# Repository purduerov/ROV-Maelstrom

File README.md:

# ROV-Maelstrom

Purdue IEEE designed an ROV (Remotely Operated underwater Vehicle) to compete in the 2016 [MATE international competition](http://www.marinetech.org/rov-competition-2/). ROV *Maelstrom* was the cumulation of this effort that resulted in a 13th place finish. For more information visit [purdueieee.org/rov](http://purdueieee.org/rov).

Our design is hearby open-sourced in order to share what we have done with other MATE teams and those who are interested. While not all of our designs worked as planned, we share these files in order to assist thoughs who may need it and inspire others with these ideas.

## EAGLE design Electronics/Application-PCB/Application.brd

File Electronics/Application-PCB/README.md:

# PCB-Maelstrom-Application
The application board was intended to contains mission specific electronics including the special manipulators, temperature sensors, pressure sensors, LED drivers, and solenoids for the claw. These components would be grouped together on this board to simplify the more complex microcontroller board with their own chip, the STM 32F405-64 PIN, to provide the interface. 

This board was planned before the mission description, but then we realized that the mission required significantly fewer tools than expected and it was easier to relocate the tooling circuitry to the main microcontroller board. However, a board was still designed for some extra features but it was never tested or implemented due to time constraints. The application board ended up including the LED drivers and the backup temperature sensor’s circuit. We kept the STM32F405-64 pin microcontroller from the original design. It also included a micro-USB for programming the STM chip, a CAN communication chip and some debugging LEDs. The LED driver was modeled to use the LM3409HV FET buck controller.

# LED driver overview
- Controlled by Texas Instruments LM3409HV Buck Controller
- Steps down Application board 12V power to 6V, 0.5A max
- Output current adjustable via PWM to allow for LED dimming
- Drives two high power white LEDs

# Main considerations taken in design of the board:
	- No ground plane or traces opposite the inductor avoid effects of eddy currents
	- Input capacitors located as close to the chip power pins on the same layer
	- Drain of PFET connected as close as possible to power inductor, with minimal trace area
	- Place output capacitor close to the inductor
	- At least 4 thermal vias located under the buck controller thermal pad for heat dissipation	
	- Isolate small signal ground (IC ground) from the power ground
	- Minimise the use of vias for the power ground
	- Isolate noise-causing components (diode, inductor, PWM signal) away from other components
	- In particular, below are the recommendations for designing the feedback route. However the design of our particular driver makes them somewhat irrelevant:
		a). Feedback terminal of IC which inputs feedback signal, is normally designed with high impedance. Output of this terminal and
		resistor crossover network must be connected with short wire.
		b). Part which detects the output voltage must be connected after output capacitor or at both ends of output capacitor.
		c). Wiring the resistor-divider circuit nearby and parallel, makes it better for noise tolerance.
		d). Draw wire far away from switching node of inductor and diode. Do not wire directly below the inductor and diode, and not
		parallel to power supply line. Multilayer board must be also wired in the same way. 
	- Proper land pattern of power components to minimize impedance: (Application Notes 136, Page 7)
		http://cds.linear.com/docs/en/application-note/an136f.pdf

(recommendations drawn from: http://rohmfs.rohm.com/en/products/databook/applinote/ic/power/switching_regulator/converter_pcb_layout_appli-e.pdf)

# Possible changes/improvements:
	- decrease the board area
	
# Thoughts:
	- The board schematic was based off the 'Typical Applications' under section 8.2 of the Buck Controller datasheet. For some reason that design does not have a output capacitor, unlike standard buck controller designs
	- The design mentioned above also uses a different feedback system compared to the standard; namely it only uses 1 resistor instead of 2

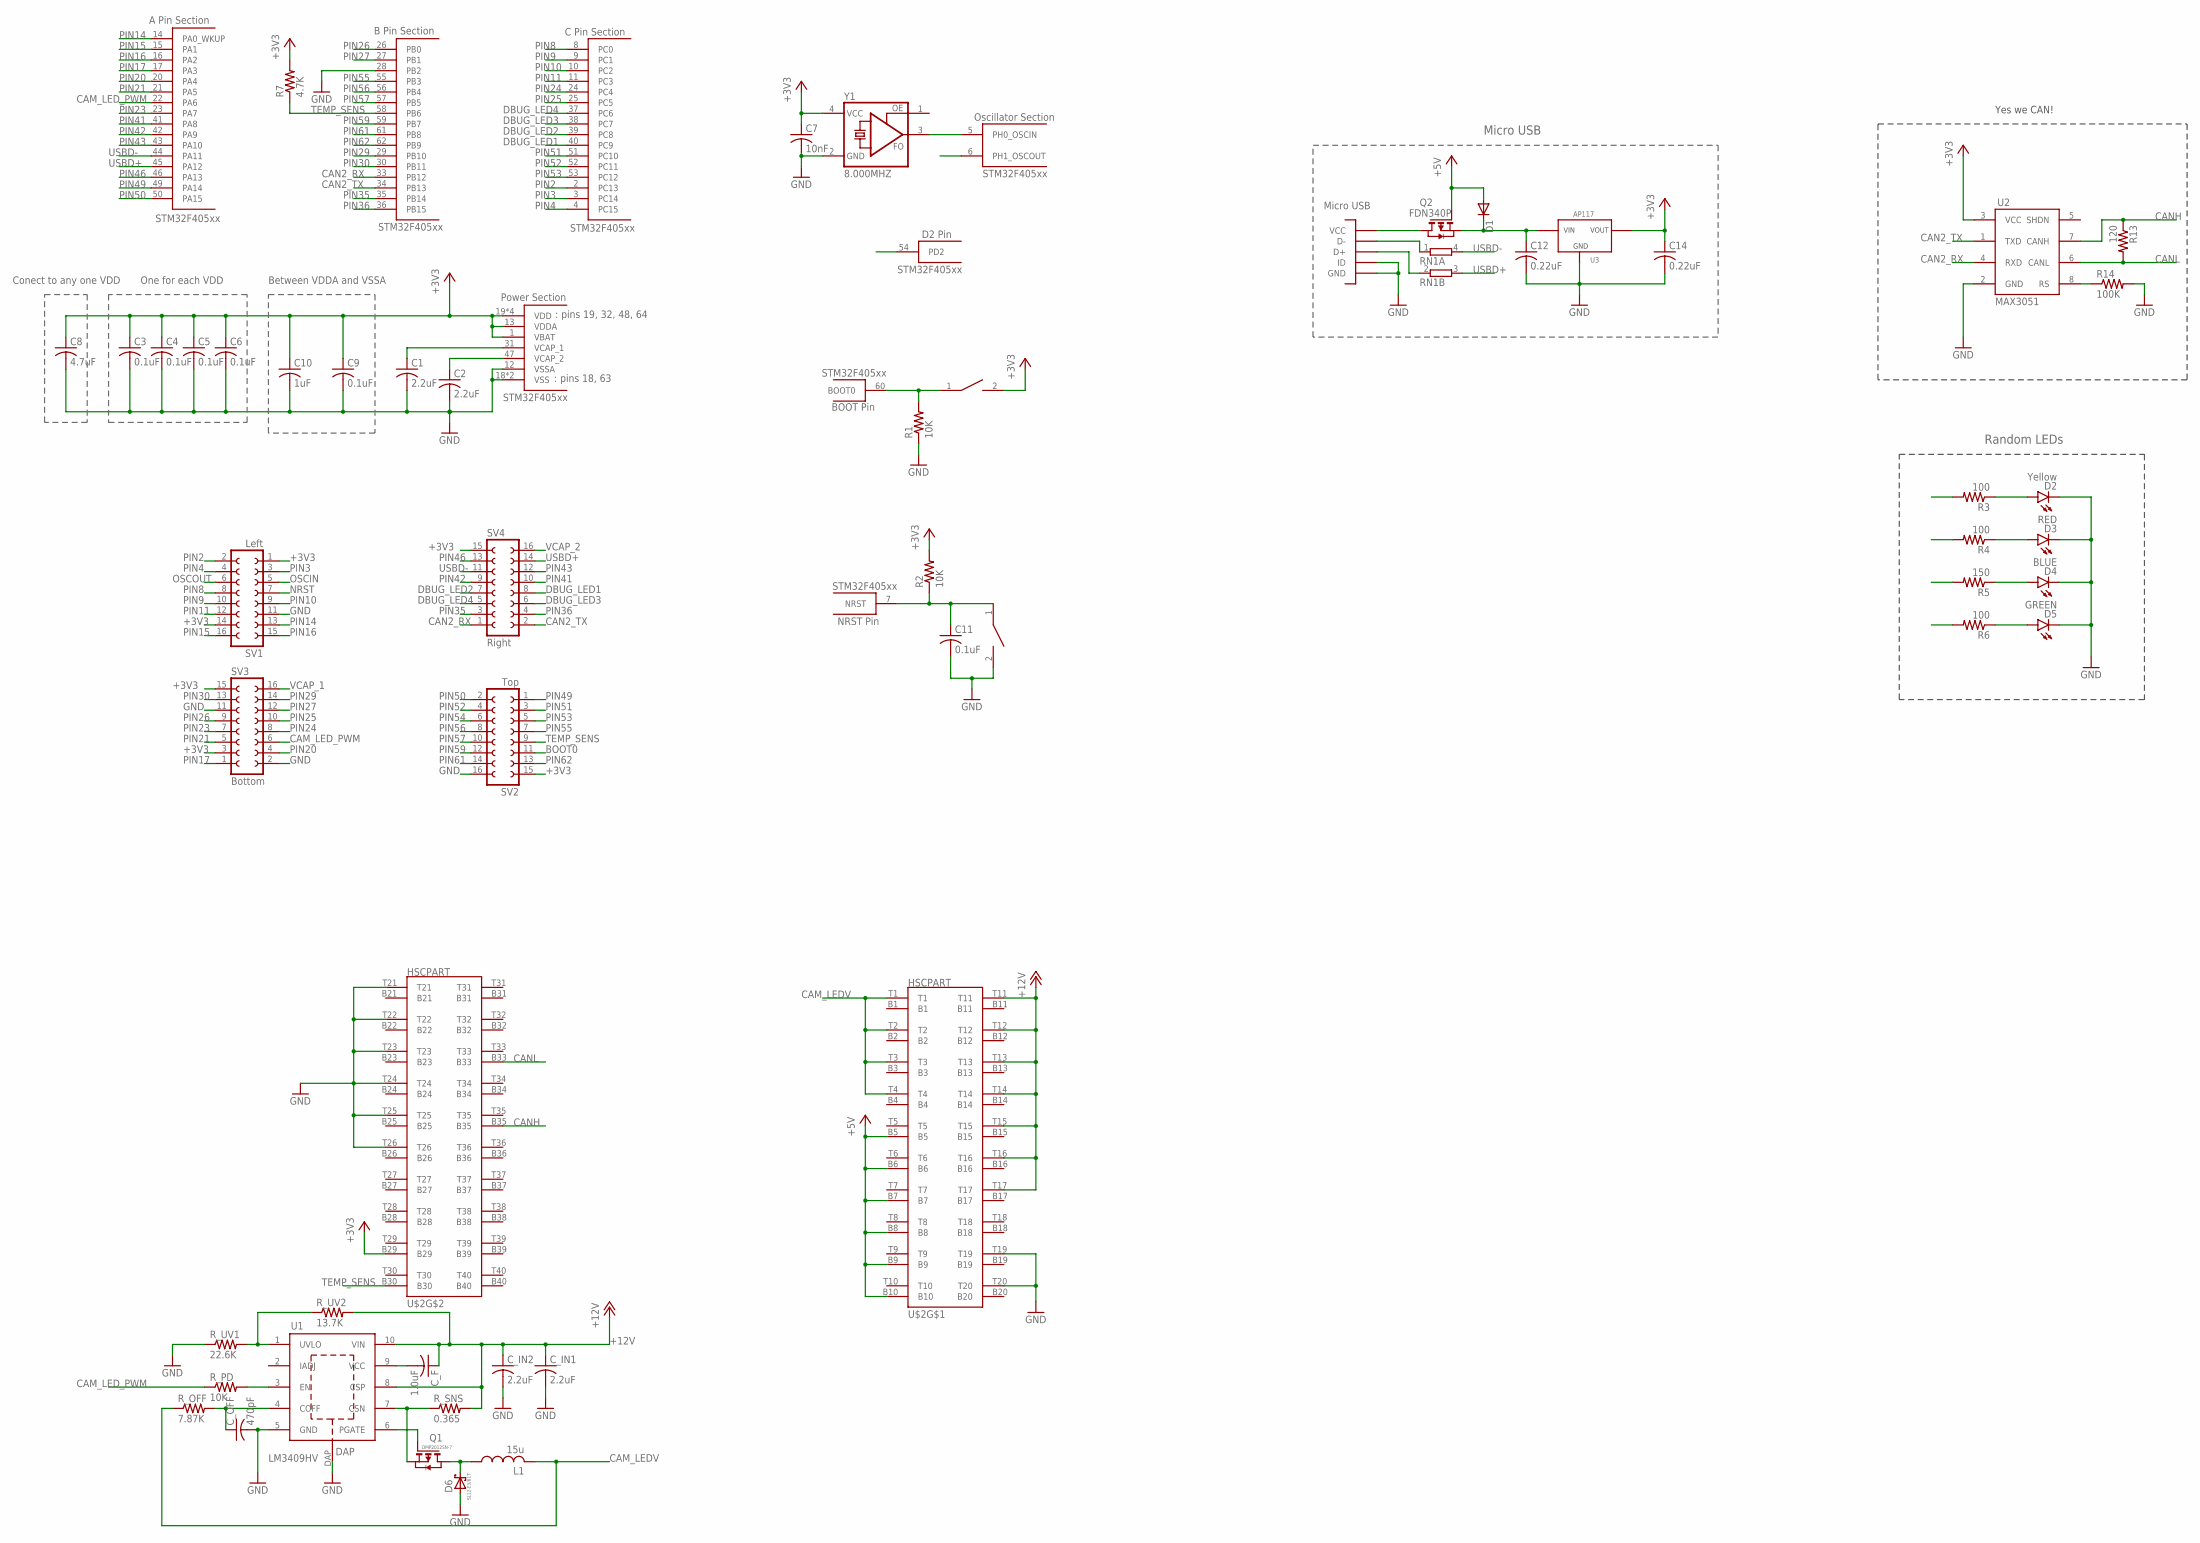
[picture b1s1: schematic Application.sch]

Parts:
C1, C2: 2.2uF; C0603
C3, C4, C5, C6, C9, C11: 0.1uF; C0603
C7: 10nF; C0603
C8: 4.7uF; C0603
C10: 1uF; C0603
C12, C14: 0.22uF; C0603
C_F: 1.0uF; C0603
C_IN1, C_IN2: 2.2uF; C0603
C_OFF: 470pF; C0603
D1: DIODE-DO-214AC; DO-214AC
D2: Yellow; LED-0603
D3: RED; LED-0603
D4: BLUE; LED-0603
D5: GREEN; LED-0603
D6: SL12-E3/61T
L1: 15u; SRN8040
Q1: DMP2012SN-7
Q2: FDN340P; SOT-23
R1, R2: 10K; R0603
R3, R4, R6: 100; R0603
R5: 150; R0603
R7: 4.7K; R0603
R13: 120; R0603
R14: 100K; R0603
RN1: 2R-NEXBV4V; EXBV4V
R_OFF: 7.87K; R0603
R_PD: 10K; R0603
R_SNS: 0.365; R2512
R_UV1: 22.6K; R0603
R_UV2: 13.7K; R0603
S1: BOOT; SW_2512
S2: RESET; SW_2512
SV1: Left; FE08-2
SV2: Top; FE08-2
SV3: Bottom; FE08-2
SV4: Right; FE08-2
U1: LM3409HV; VSSOP-10
U2: MAX3051; SOT23-8L
U3: U3; SOT223
U4: STM32F405; LQFP64
U5: MICROUSB; MICRO_B
U$2: HSCPART; HSC8-40PINOUUT
Y1: 8.000MHZ; ASF

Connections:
+3V3: C3.1, C4.1, C5.1, C6.1, C7.1, C8.1, C9.1, C10.1, C14.1, R2.2, R7.2, S1.2, SV1.1, SV1.14, SV2.15, SV3.3, SV3.15, SV4.15, U2.3 (VCC), U3.TAB (VOUT), U3.VOUT, U4.1 (VBAT), U4.13 (VDDA), U4.19 (VDD), U4.32 (VDD), U4.48 (VDD), U4.64 (VDD), U$2.B29, Y1.4 (VCC)
+5V: D1.A, Q2.3 (G), U$2.B5, U$2.B6, U$2.B7, U$2.B8, U$2.B9, U$2.B10
+12V: C_F.1, C_IN1.1, C_IN2.1, R_SNS.2, R_UV2.2, U1.8 (CSP), U1.10 (VIN), U$2.T11, U$2.T12, U$2.T13, U$2.T14, U$2.T15, U$2.T16, U$2.T17
BOOT0: R1.2, S1.1, SV2.11, U4.60 (BOOT0)
CAM_LEDV: L1.2, R_OFF.1, U$2.T1, U$2.T2, U$2.T3, U$2.T4
CAM_LED_PWM: R_PD.1, SV3.6, U4.22 (PA6)
CAN2_RX: SV4.1, U2.4 (RXD), U4.33 (PB12)
CAN2_TX: SV4.2, U2.1 (TXD), U4.34 (PB13)
CANH: R13.1, U2.7 (CANH), U$2.B35
CANL: R13.2, U2.6 (CANL), U$2.B33
DBUG_LED1: R3.2, SV4.8, U4.40 (PC9)
DBUG_LED2: R4.2, SV4.7, U4.39 (PC8)
DBUG_LED3: R5.2, SV4.6, U4.38 (PC7)
DBUG_LED4: R6.2, SV4.5, U4.37 (PC6)
GND: C1.2, C2.2, C3.2, C4.2, C5.2, C6.2, C7.2, C8.2, C9.2, C10.2, C11.2, C12.2, C14.2, C_IN1.2, C_IN2.2, C_OFF.2, D2.C, D3.C, D4.C, D5.C, D6.2 (A), R1.1, R14.2, R_UV1.1, S2.2, SV1.11, SV2.16, SV3.2, SV3.11, U1.5 (GND), U1.DAP, U2.2 (GND), U3.GND, U4.12 (VSSA), U4.18 (VSS), U4.28 (PB2), U4.63 (VSS), U5.GND1 (GND), U5.GND2 (GND), U5.GND3 (GND), U5.GND4 (GND), U5.GND7 (GND), U5.GND8 (GND), U5.P4 (ID), U5.P5 (GND), U$2.T19, U$2.T20, U$2.T21, U$2.T22, U$2.T23, U$2.T24, U$2.T25, U$2.T26, Y1.2 (GND)
L1: D6.1 (C), L1.1, Q1.1 (D)
unnamed: RN1.1, U5.P2 (D-)
unnamed: R_UV1.2, R_UV2.1, U1.1 (UVLO)
unnamed: C_OFF.1, R_OFF.2, U1.4 (COFF)
unnamed: C_F.2, U1.9 (VCC)
unnamed: Q1.3 (S), R_SNS.1, U1.7 (CSN)
unnamed: R_PD.2, U1.3 (EN)
unnamed: Q1.2 (G), U1.6 (PGATE)
unnamed: RN1.2 (1), U5.P3 (D+)
unnamed: Q2.1 (D), U5.P1 (VCC)
unnamed: C12.1, D1.C, Q2.2 (S), U3.VIN
unnamed: D2.A, R3.1
unnamed: D3.A, R4.1
unnamed: D4.A, R5.1
unnamed: D5.A, R6.1
unnamed: R14.1, U2.8 (RS)
NRST: C11.1, R2.1, S2.1, SV1.7, U4.7 (NRST)
OSCIN: SV1.5, U4.5 (PH0_OSCIN), Y1.3 (FO)
OSCOUT: SV1.6, U4.6 (PH1_OSCOUT)
PIN2: SV1.2, U4.2 (PC13)
PIN3: SV1.3, U4.3 (PC14)
PIN4: SV1.4, U4.4 (PC15)
PIN8: SV1.8, U4.8 (PC0)
PIN9: SV1.10, U4.9 (PC1)
PIN10: SV1.9, U4.10 (PC2)
PIN11: SV1.12, U4.11 (PC3)
PIN14: SV1.13, U4.14 (PA0_WKUP)
PIN15: SV1.16, U4.15 (PA1)
PIN16: SV1.15, U4.16 (PA2)
PIN17: SV3.1, U4.17 (PA3)
PIN20: SV3.4, U4.20 (PA4)
PIN21: SV3.5, U4.21 (PA5)
PIN23: SV3.7, U4.23 (PA7)
PIN24: SV3.8, U4.24 (PC4)
PIN25: SV3.10, U4.25 (PC5)
PIN26: SV3.9, U4.26 (PB0)
PIN27: SV3.12, U4.27 (PB1)
PIN29: SV3.14, U4.29 (PB10)
PIN30: SV3.13, U4.30 (PB11)
PIN35: SV4.3, U4.35 (PB14)
PIN36: SV4.4, U4.36 (PB15)
PIN41: SV4.10, U4.41 (PA8)
PIN42: SV4.9, U4.42 (PA9)
PIN43: SV4.12, U4.43 (PA10)
PIN46: SV4.13, U4.46 (PA13)
PIN49: SV2.1, U4.49 (PA14)
PIN50: SV2.2, U4.50 (PA15)
PIN51: SV2.3, U4.51 (PC10)
PIN52: SV2.4, U4.52 (PC11)
PIN53: SV2.5, U4.53 (PC12)
PIN54: SV2.6, U4.54 (PD2)
PIN55: SV2.7, U4.55 (PB3)
PIN56: SV2.8, U4.56 (PB4)
PIN57: SV2.10, U4.57 (PB5)
PIN59: SV2.12, U4.59 (PB7)
PIN61: SV2.14, U4.61 (PB8)
PIN62: SV2.13, U4.62 (PB9)
TEMP_SENS: R7.1, SV2.9, U4.58 (PB6), U$2.B30
USBD+: RN1.3 (2), SV4.14, U4.45 (PA12)
USBD-: RN1.4 (2), SV4.11, U4.44 (PA11)
VCAP_1: C1.1, SV3.16, U4.31 (VCAP_1)
VCAP_2: C2.1, SV4.16, U4.47 (VCAP_2)

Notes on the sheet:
: pins 19, 32, 48, 64
: pins 18, 63
Between VDDA and VSSA
One for each VDD
Conect to any one VDD
Micro USB
Yes we CAN!
Random LEDs

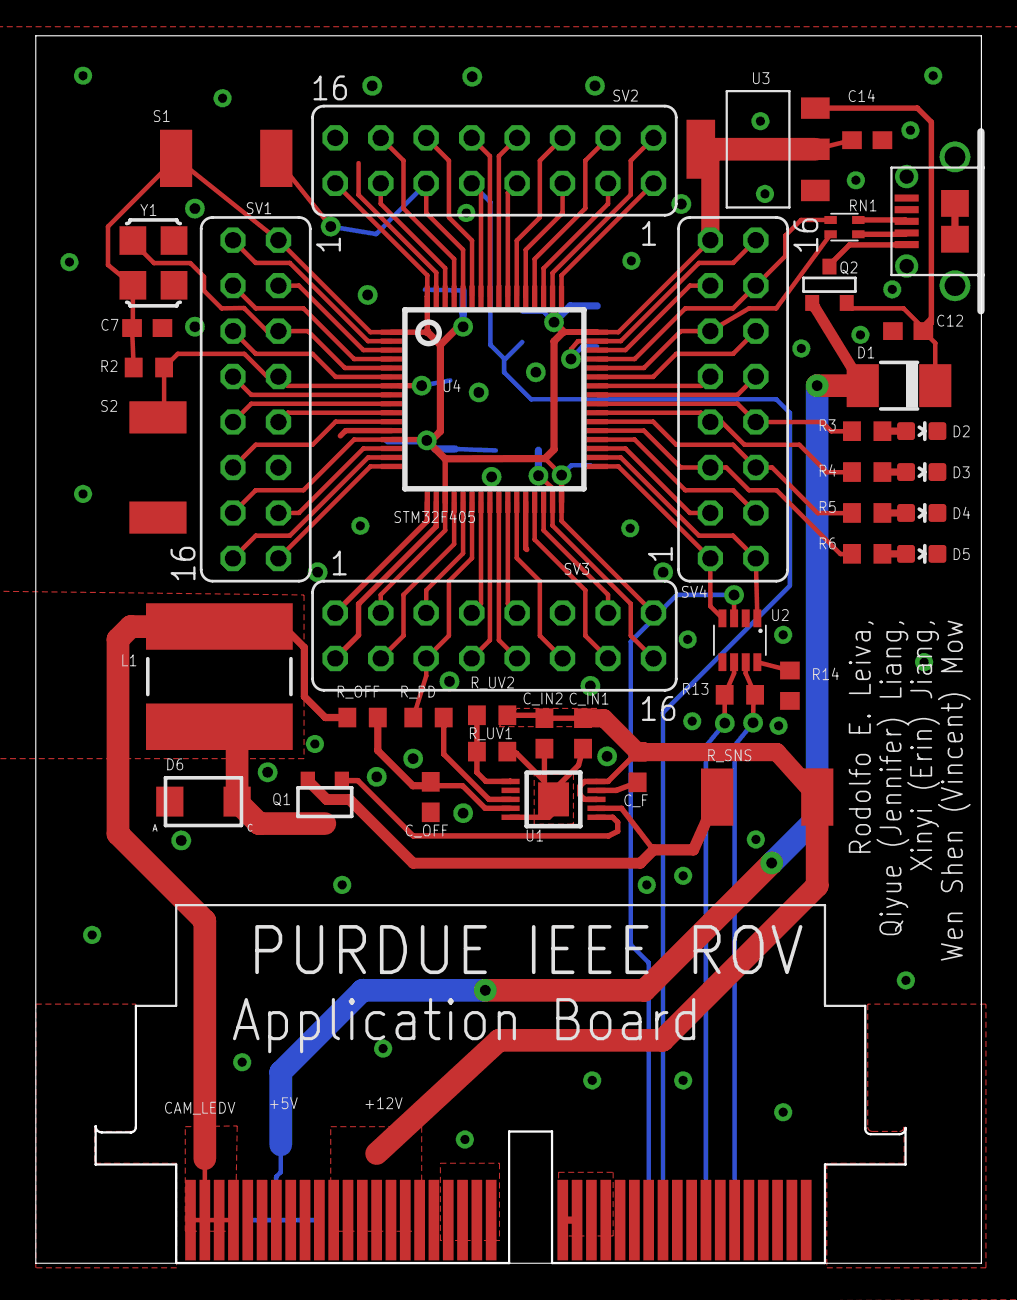
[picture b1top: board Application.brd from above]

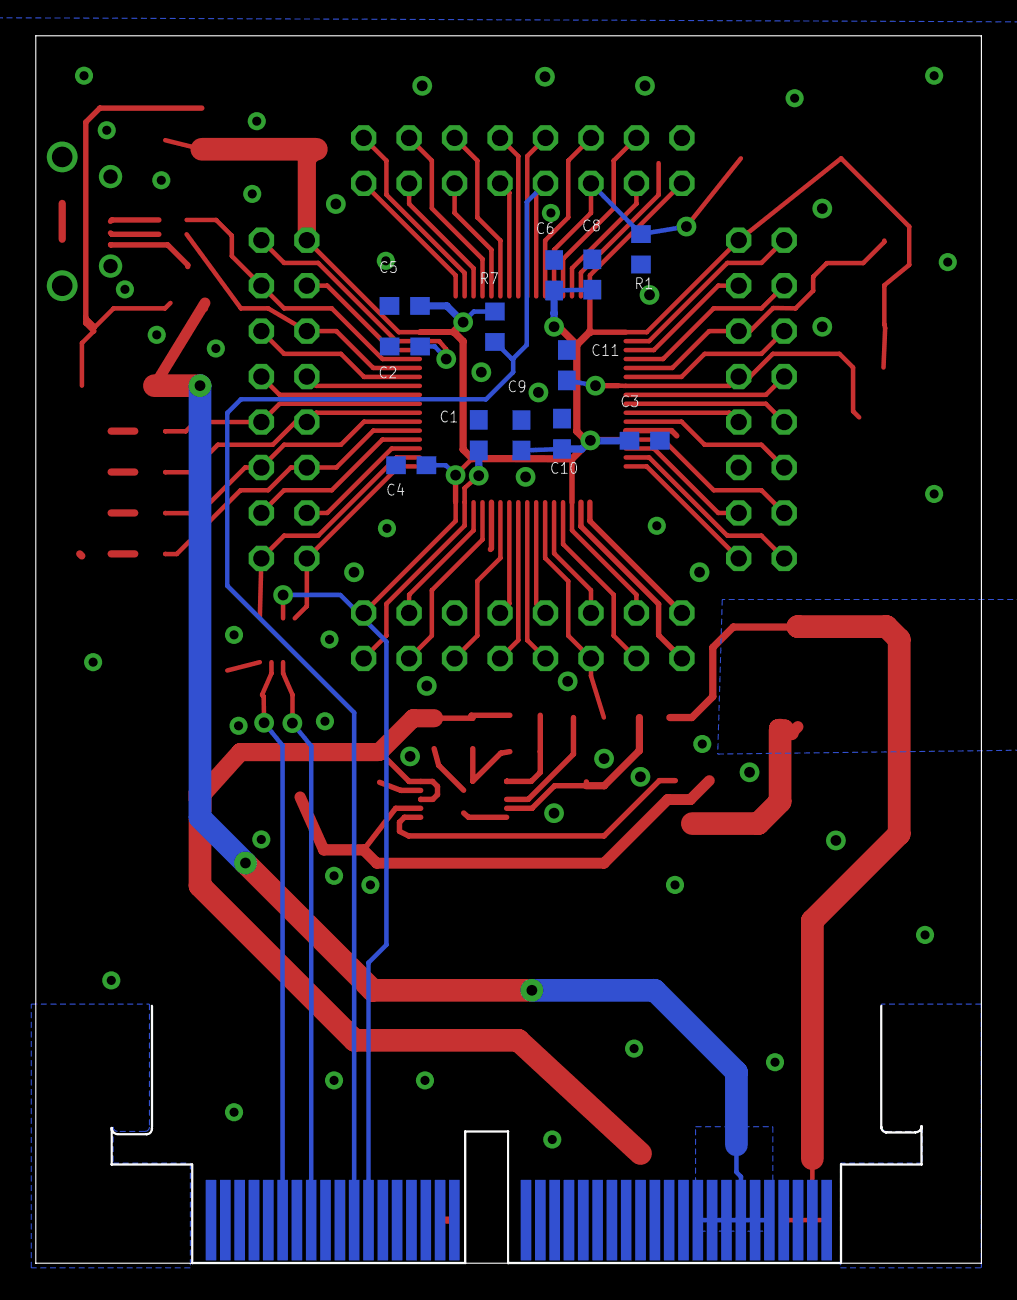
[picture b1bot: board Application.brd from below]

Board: 2 copper layers, 52.8 x 68.6 mm, 54 parts (12 on the bottom side), 77 nets.

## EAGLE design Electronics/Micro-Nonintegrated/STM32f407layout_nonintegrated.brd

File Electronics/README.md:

# ROV-Maelstrom-Electronics

ROV Maelstrom’s electronics were designed to facilitate easy and reliable command over the course of the ROV’s lifetime. Command starts at the Control Center, the surface electronics that the user interfaces with. This includes a laptop computer, a network router, and a 48 V power supply protected with a 40-A fuse. 

Communication with the Control Center is done through the tether with a Category 5 Ethernet cable, which provides high bandwidth and noise immunity. The power is transmitted through two 12-AWG marine wires. Onboard the ROV, it steps down the 48 V to 12 V, 5 V, and 3.3 V for use by the ROV’s eight T200 thrusters, the hydraulics motor, and the Main Electronics inside the Electronics Tube. The Power Distribution Box contains the Power Distribution Board, which handles the 48 V to 12 V power conversion and thruster control. Inside of the Electronics Tube are the Main Microcontroller Board, the Power Regulator Board, and the Application Board which are all connected via the Backplane. The Main Microcontroller Board handles the central logic processing of the ROV and communication with the surface, Application Board, and Power Distribution Board. The Power Regulator Board supplies the 5 V required by the electronics inside of the Electronics Tube, while the Application Board controls the LED lighting of ROV Maelstrom. The Navigation Board is used for pressure and attitude measurements and is placed outside of the Electronics Tube for reduced magnetic interference and direct contact with water. The board also hosts the sonar transmitter used for GPS-like navigation. The Sonar Receiver Board in the Control Center is used to receive and filter the sonar transmission signals. The printed circuit boards were designed in-house with the use of CadSoft's EAGLE software and then hand populated

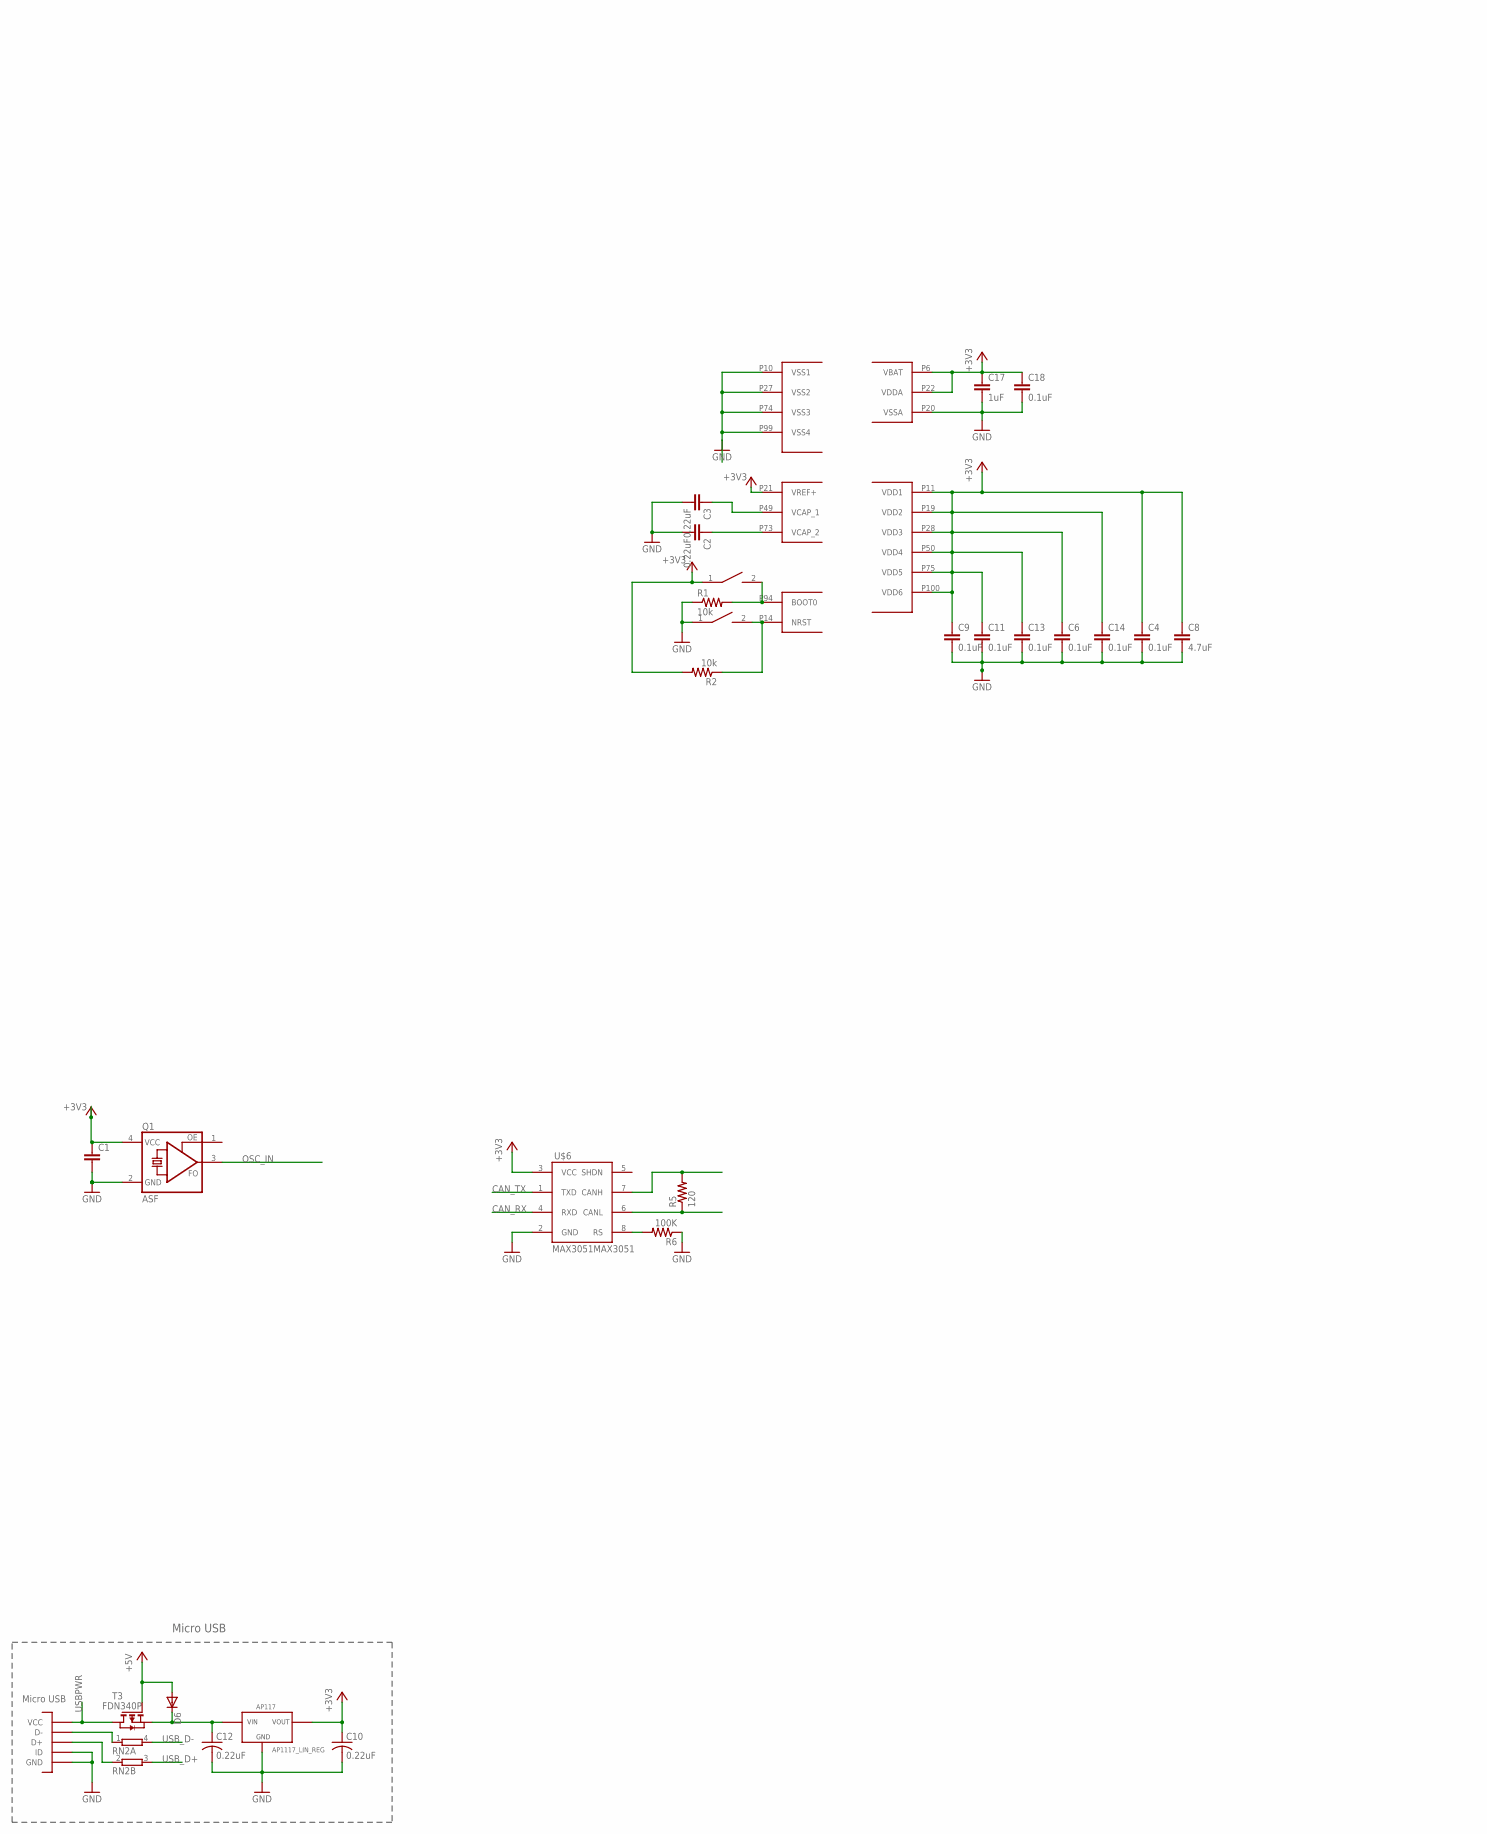
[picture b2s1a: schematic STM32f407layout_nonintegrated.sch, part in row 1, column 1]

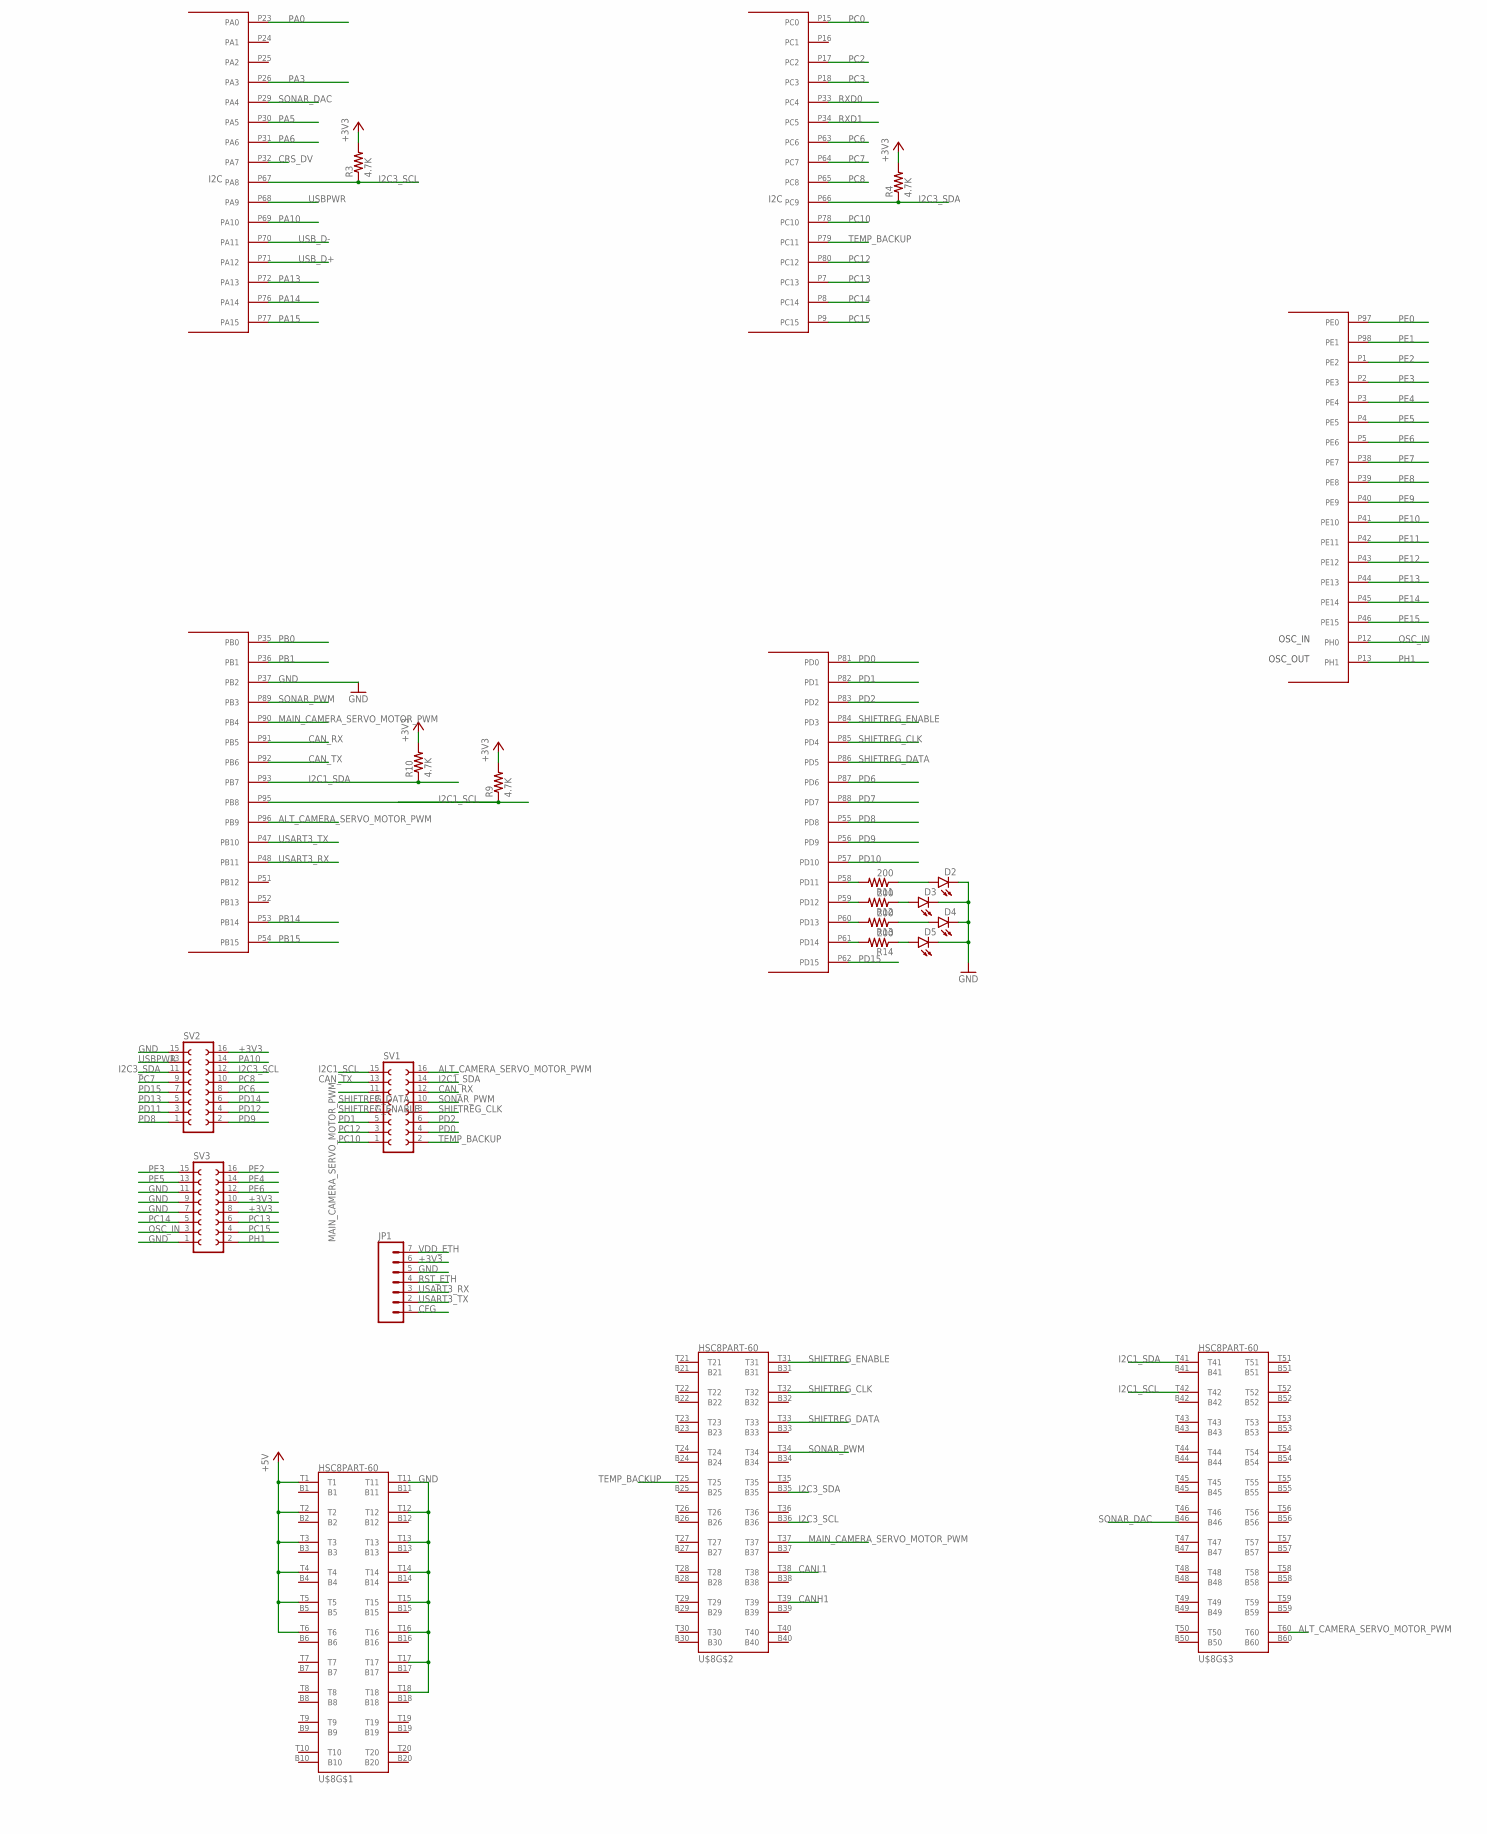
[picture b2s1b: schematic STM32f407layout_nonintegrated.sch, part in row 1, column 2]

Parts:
C1: CAP0603-CAP; 0603-CAP
C2, C3: 0.22uF; 0603-CAP
C4, C6, C9, C11, C13, C14, C18: 0.1uF; 0603-CAP
C8: 4.7uF; 0603-CAP
C10, C12: 0.22uF; C0603
C17: 1uF; 0603-CAP
D2, D3, D4, D5: LED0603; LED-0603
D6: DIODE-DO-214AC; DO-214AC
JP1: M07; 1X07
Q1: ASF
R1, R2: 10k; 0603-RES
R3, R4, R9, R10: 4.7K; 0603-RES
R5: 120; 0603-RES
R6: 100K; 0603-RES
R11, R12, R13, R14: 200; 0603-RES
RN2: 2R-NEXBV4V; EXBV4V
SV1, SV2, SV3: FE08-2
T3: FDN340P; SOT-23
T4: AP1117_LIN_REG; SOT223
U$1: STM32F4; LQFP100
U$2, U$3: SWITCH; SW_2512
U$5: MICROUSB; MICRO_B
U$6: MAX3051MAX3051; SOT23-8L
U$8: HSC8PART-60; HSC8-60PINOUUT

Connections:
+3V3: C1.1, C4.1, C6.1, C8.1, C9.1, C10.1, C11.1, C13.1, C14.1, C17.1, C18.1, JP1.6, Q1.4 (VCC), R2.2, R3.2, R4.2, R9.2, R10.2, SV2.16, SV3.8, SV3.10, T4.TAB (VOUT), T4.VOUT, U$1.P6 (VBAT), U$1.P11 (VDD1), U$1.P19 (VDD2), U$1.P21 (VREF+), U$1.P22 (VDDA), U$1.P28 (VDD3), U$1.P50 (VDD4), U$1.P75 (VDD5), U$1.P100 (VDD6), U$3.1, U$6.3 (VCC)
+5V: D6.A, T3.3 (G), U$8.T1, U$8.T2, U$8.T3, U$8.T4, U$8.T5, U$8.T6
ALT_CAMERA_SERVO_MOTOR_PWM: SV1.16, U$1.P96 (PB9), U$8.T60
CANH1: R5.2, U$6.7 (CANH), U$8.T39
CANL1: R5.1, U$6.6 (CANL), U$8.T38
CAN_RX: SV1.12, U$1.P91 (PB5), U$6.4 (RXD)
CAN_TX: SV1.13, U$1.P92 (PB6), U$6.1 (TXD)
CFG: JP1.1
CRS_DV: U$1.P32 (PA7)
GND: C1.2, C2.2, C3.2, C4.2, C6.2, C8.2, C9.2, C10.2, C11.2, C12.2, C13.2, C14.2, C17.2, C18.2, D2.C, D3.C, D4.C, D5.C, JP1.5, Q1.2 (GND), R1.1, R6.1, SV2.15, SV3.1, SV3.7, SV3.9, SV3.11, T4.GND, U$1.P10 (VSS1), U$1.P20 (VSSA), U$1.P27 (VSS2), U$1.P37 (PB2), U$1.P74 (VSS3), U$1.P99 (VSS4), U$2.1, U$5.GND1 (GND), U$5.GND2 (GND), U$5.GND3 (GND), U$5.GND4 (GND), U$5.GND7 (GND), U$5.GND8 (GND), U$5.P4 (ID), U$5.P5 (GND), U$6.2 (GND), U$8.T11, U$8.T12, U$8.T13, U$8.T14, U$8.T15, U$8.T16, U$8.T17, U$8.T18
I2C1_SCL: R9.1, SV1.15, U$1.P95 (PB8), U$8.T42
I2C1_SDA: R10.1, SV1.14, U$1.P93 (PB7), U$8.T41
I2C3_SCL: R3.1, SV2.12, U$1.P67 (PA8), U$8.B36
I2C3_SDA: R4.1, SV2.11, U$1.P66 (PC9), U$8.B35
MAIN_CAMERA_SERVO_MOTOR_PWM: SV1.11, U$1.P90 (PB4), U$8.T37
unnamed: C2.1, U$1.P73 (VCAP_2)
unnamed: C3.1, U$1.P49 (VCAP_1)
unnamed: R1.2, U$1.P94 (BOOT0), U$3.2
unnamed: R2.1, U$1.P14 (NRST), U$2.2
unnamed: R6.2, U$6.8 (RS)
unnamed: RN2.1, U$5.P2 (D-)
unnamed: D3.A, R12.1
unnamed: D5.A, R14.1
unnamed: D4.A, R13.1
unnamed: D2.A, R11.1
unnamed: RN2.2 (1), U$5.P3 (D+)
unnamed: C12.1, D6.C, T3.2 (S), T4.VIN
OSC_IN: Q1.3 (FO), SV3.3, U$1.P12 (PH0)
PA0: U$1.P23 (PA0)
PA3: U$1.P26 (PA3)
PA5: U$1.P30 (PA5)
PA6: U$1.P31 (PA6)
PA10: SV2.14, U$1.P69 (PA10)
PA13: U$1.P72 (PA13)
PA14: U$1.P76 (PA14)
PA15: U$1.P77 (PA15)
PB0: U$1.P35 (PB0)
PB1: U$1.P36 (PB1)
PB14: U$1.P53 (PB14)
PB15: U$1.P54 (PB15)
PC0: U$1.P15 (PC0)
PC2: U$1.P17 (PC2)
PC3: U$1.P18 (PC3)
PC6: SV2.8, U$1.P63 (PC6)
PC7: SV2.9, U$1.P64 (PC7)
PC8: SV2.10, U$1.P65 (PC8)
PC10: SV1.1, U$1.P78 (PC10)
PC12: SV1.3, U$1.P80 (PC12)
PC13: SV3.6, U$1.P7 (PC13)
PC14: SV3.5, U$1.P8 (PC14)
PC15: SV3.4, U$1.P9 (PC15)
PD0: SV1.4, U$1.P81 (PD0)
PD1: SV1.5, U$1.P82 (PD1)
PD2: SV1.6, U$1.P83 (PD2)
PD6: U$1.P87 (PD6)
PD7: U$1.P88 (PD7)
PD8: SV2.1, U$1.P55 (PD8)
PD9: SV2.2, U$1.P56 (PD9)
PD10: U$1.P57 (PD10)
PD11: R11.2, SV2.3, U$1.P58 (PD11)
PD12: R12.2, SV2.4, U$1.P59 (PD12)
PD13: R13.2, SV2.5, U$1.P60 (PD13)
PD14: R14.2, SV2.6, U$1.P61 (PD14)
PD15: SV2.7, U$1.P62 (PD15)
PE0: U$1.P97 (PE0)
PE1: U$1.P98 (PE1)
PE2: SV3.16, U$1.P1 (PE2)
PE3: SV3.15, U$1.P2 (PE3)
PE4: SV3.14, U$1.P3 (PE4)
PE5: SV3.13, U$1.P4 (PE5)
PE6: SV3.12, U$1.P5 (PE6)
PE7: U$1.P38 (PE7)
PE8: U$1.P39 (PE8)
PE9: U$1.P40 (PE9)
PE10: U$1.P41 (PE10)
PE11: U$1.P42 (PE11)
PE12: U$1.P43 (PE12)
PE13: U$1.P44 (PE13)
PE14: U$1.P45 (PE14)
PE15: U$1.P46 (PE15)
PH1: SV3.2, U$1.P13 (PH1)
RST_ETH: JP1.4
RXD0: U$1.P33 (PC4)
RXD1: U$1.P34 (PC5)
SHIFTREG_CLK: SV1.8, U$1.P85 (PD4), U$8.T32
SHIFTREG_DATA: SV1.9, U$1.P86 (PD5), U$8.T33
SHIFTREG_ENABLE: SV1.7, U$1.P84 (PD3), U$8.T31
SONAR_DAC: U$1.P29 (PA4), U$8.B46
SONAR_PWM: SV1.10, U$1.P89 (PB3), U$8.T34
TEMP_BACKUP: SV1.2, U$1.P79 (PC11), U$8.T25
USART3_RX: JP1.3, U$1.P48 (PB11)
USART3_TX: JP1.2, U$1.P47 (PB10)
USBPWR: SV2.13, T3.1 (D), U$1.P68 (PA9), U$5.P1 (VCC)
USB_D+: RN2.3 (2), U$1.P71 (PA12)
USB_D-: RN2.4 (2), U$1.P70 (PA11)
VDD_ETH: JP1.7

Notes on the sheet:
I2C
Micro USB

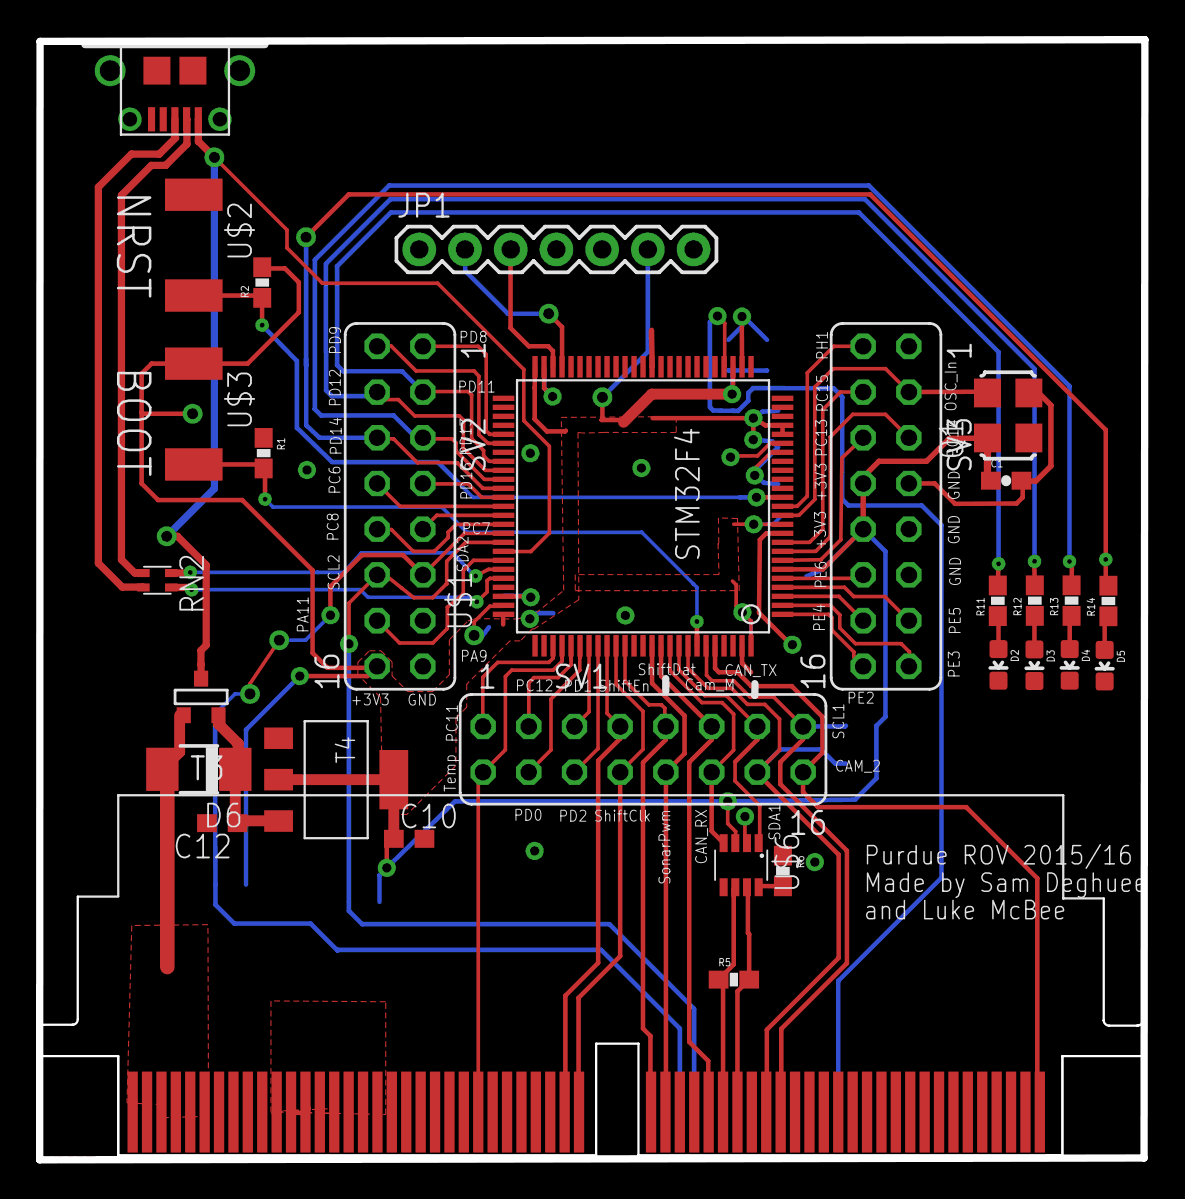
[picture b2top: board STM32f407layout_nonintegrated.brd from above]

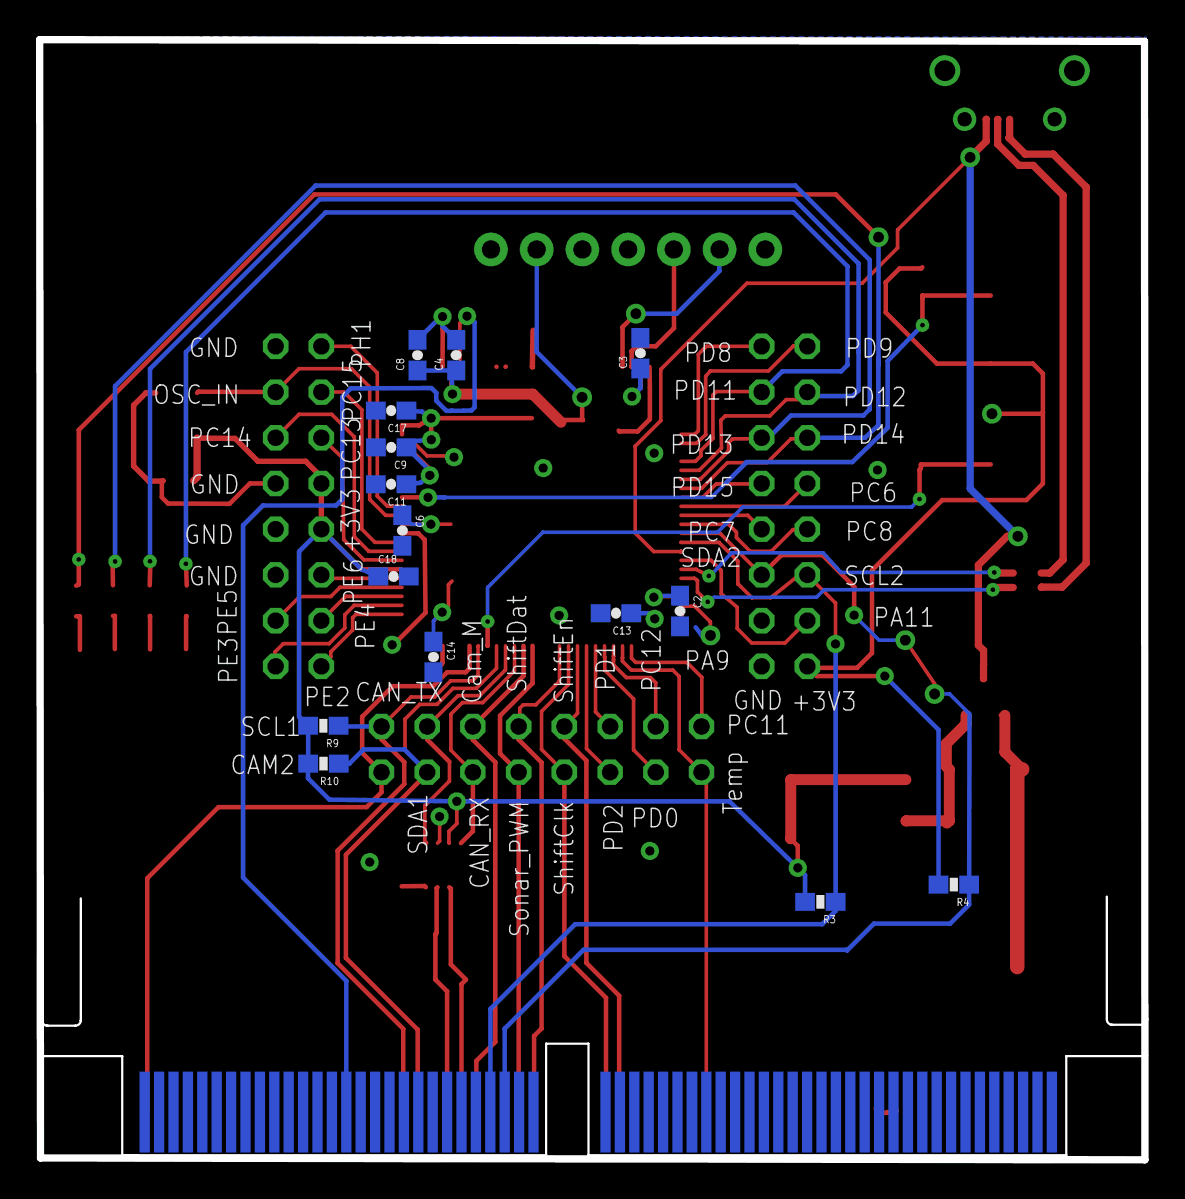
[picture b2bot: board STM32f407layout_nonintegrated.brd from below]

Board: 2 copper layers, 61.4 x 62.2 mm, 45 parts (15 on the bottom side), 62 nets.

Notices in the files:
parts and their libraries:
SparkFun-LED: Licensing: Creative Commons ShareAlike 4.0 International - https://creativecommons.org/licenses/by-sa/4.0
SparkFun: Licensing: CC v3.0 Share-Alike You are welcome to use this library for commercial purposes.
